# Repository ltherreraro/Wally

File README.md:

# Wally
## Recolector de basura espacios cerrados usando esp32 y RP2040
Es un dispositivo robótico con capacidad de navegación por  espacios abiertos y cerrados, reconocimiento y transmisión de imagen y video, con la finalidad de ver e identificar objetos del entorno y disponer de ellos (levantarlos, recogerlos y llevarlos a un sitio específico).  Inicialmente pensado para labores de aseo, puede ser fácilmente utilizado en otros entornos que por sus condiciones  representen un riesgo para la vida humana y animal (recintos con riesgos biológicos, edificios al borde del colapso, entre otros), que se puede validar a traves de una aplicacion
### ALCANCE
Durante la primera iteración, estamos trabajando para que Wally pueda recorrer un espacio cerrado relativamente pequeño (por ejemplo, un salón) evitando obstaculos y la identificación de objetos a través de la cámara de manera limitada.
### REQUERIMENTOS FUNCIONALES
Recepción y transmisión de imágenes, streaming video, detección de imágenes vía imagen y sensor ultrasonido, capacidad de navegación, recolección del objeto, conectividad inalámbrica (Wi-Fi, Bluetooth).
###REQUERIMENTOS NO FUNCIONALES
Estabilidad, fiabilidad, precisión el el reconocimiento y recolección de objeto, facilidad de uso.
### 
| Equipo | Corriente (in)| Voltaje (in)  |
| ------------- | ------------- |------------  |
| ESP32CAM | 500mA  |  3.3V -5V |
| NODEMCU  | 300mA  |  3,3V - 5V |
| SERVOR  | 400mA  |   5V |
| MOTOR  | 400mA  | 6V-9V |
| ULTRASONIO  | 15mA  |  5V  |
| L9110(PUENTE H)  | 0.5mA  | 2.5V-12V |
| MORSUN  | 800mA  |4.5v-36v  |

MORSUN: Salida 2000mA a 5V o 3,3V
### DIAGRAMA CAJA NEGRA
El módulo ESP32-CAM  sera el modulo principal tiene algunas características técnicas como son:

- Conectividad: WiFi 802.11b/g/n + Bluetooth 4.2 con BLE. Soporta carga de imagen por WiFi.
- Conexiones: UART, SPI, I2C, y PWM. Tiene 9 pines GPIO.
- Frecuencia de reloj: hasta 160Mhz.
- Potencia de cómputo del microcontrolador: hasta 600 DMIPS.
- Memoria: 520KB de SRAM +  4MB de PSRAM + SD slot para tarjetas
- Extras: tiene múltiples modos de reposo, firmware actualizable por OTA, y LED para uso de memoria flash built-in.
- Cámara: soporta cámaras OV2640 que pueden venir en el pack o comprarse independientemente. Este tipo de cámaras tienen:
- 2 MP en su sensor
- Tamaño de arreglo UXGA de 1622×1200 px
- Formato de salida YUV422, YUV420, RGB565, RGB555 y compresión de datos de 8-bit.
- Puede transferir imagen entre 15 y 60 FPS.

Adicionalmente se usara un modulo secundario ESP8266 para el control de los motores y **modulo ultrasonido**, el sistema en general tiene diferentes modulos como:
* Modulo de alimentacion: Consta de la bateria y el sistema de regulacion
* Modulo de movimiento: Inicialmente se plantea que se requiere un puente H de dos canales y dos motores.
* Modulo de movimiento detecion: Consta de un servomotor de 360 grados para rotar la camara 360
* Modulo de movimiento recolección: Inicialmente se plantea como dos servomotores
* Modulo de deteccion: Consta de una camara para reconocer basura y ultrasonido para detectar obstaculos tambien la cercania de los objetos
* Modulo de Indicadores y botones: Consta de leds para notificar al usuario conexion con el servidor, encendido, falla y botones de encendido tambien de reset.
 Modulo SD: Que se encargara de guardar las imagenes para ser enviadas en caso de perdida de conexion.

A continuacion se muestra un diagrama general

Finalmente los datasheet de los modulos a usar
- [ESP32](https://github.com/ltherreraro/Wally/blob/main/Datasheet/esp32-sl_specification.pdf)
- [ESP32CAM](https://github.com/ltherreraro/Wally/blob/main/Datasheet/ESP32-CAM%20Product%20Specification.pdf)
- [Nodemcu](https://www.make-it.ca/nodemcu-details-specifications/)
- [ESP8266](https://github.com/ltherreraro/Wally/blob/main/Datasheet/0a-esp8266ex_datasheet_en.pdf)
- [Servo MG90](https://github.com/ltherreraro/Wally/blob/main/Datasheet/MG90S_Tower-Pro%20(1).pdf)
- [Servo SG90](https://github.com/ltherreraro/Wally/blob/main/Datasheet/sg90_datasheet%20(1).pdf)
- [Motor](https://ferretronica.com/products/motorreductor-500-gr-cm-1000-rpm-6v?variant=12391693877341&currency=COP&utm_medium=product_sync&utm_source=google&utm_content=sag_organic&utm_campaign=sag_organic&utm_campaign=gs-2021-10-19&utm_source=google&utm_medium=smart_campaign&gclid=Cj0KCQjwjbyYBhCdARIsAArC6LKaKwvKPRHye8ZWSAgEkHbSm4rjs0Gm-KYxnCncWKSN3TIoLXUkZbEaAqU5EALw_wcB)
- [Ultrasonido](https://github.com/ltherreraro/Wally/blob/main/Datasheet/HCSR04%20(1).pdf)
- [Puente H](https://github.com/ltherreraro/Wally/blob/main/Datasheet/datasheet-l9110%20(1).pdf)
- [Regulador](https://github.com/ltherreraro/Wally/blob/main/Datasheet/2001081204_Shikues-AMS1117-1-2_C475600.pdf)
- [RP2040 pico](https://github.com/ltherreraro/Wally/blob/main/Datasheet/rp2040-datasheet.pdf)

#### Placa fabricada (Embebido)
Para este proyecto se diseño una placa con las condiciones necesarias para soportar el proyecto requerido, tanto en las corrientes que se aplican como en los circuitor integrados, dando como resultado, despues de impresión y ensamble, la siguiente placa: 

)
)
)

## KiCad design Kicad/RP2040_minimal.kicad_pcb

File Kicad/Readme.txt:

Vivan las drogas y el rock n roll!!

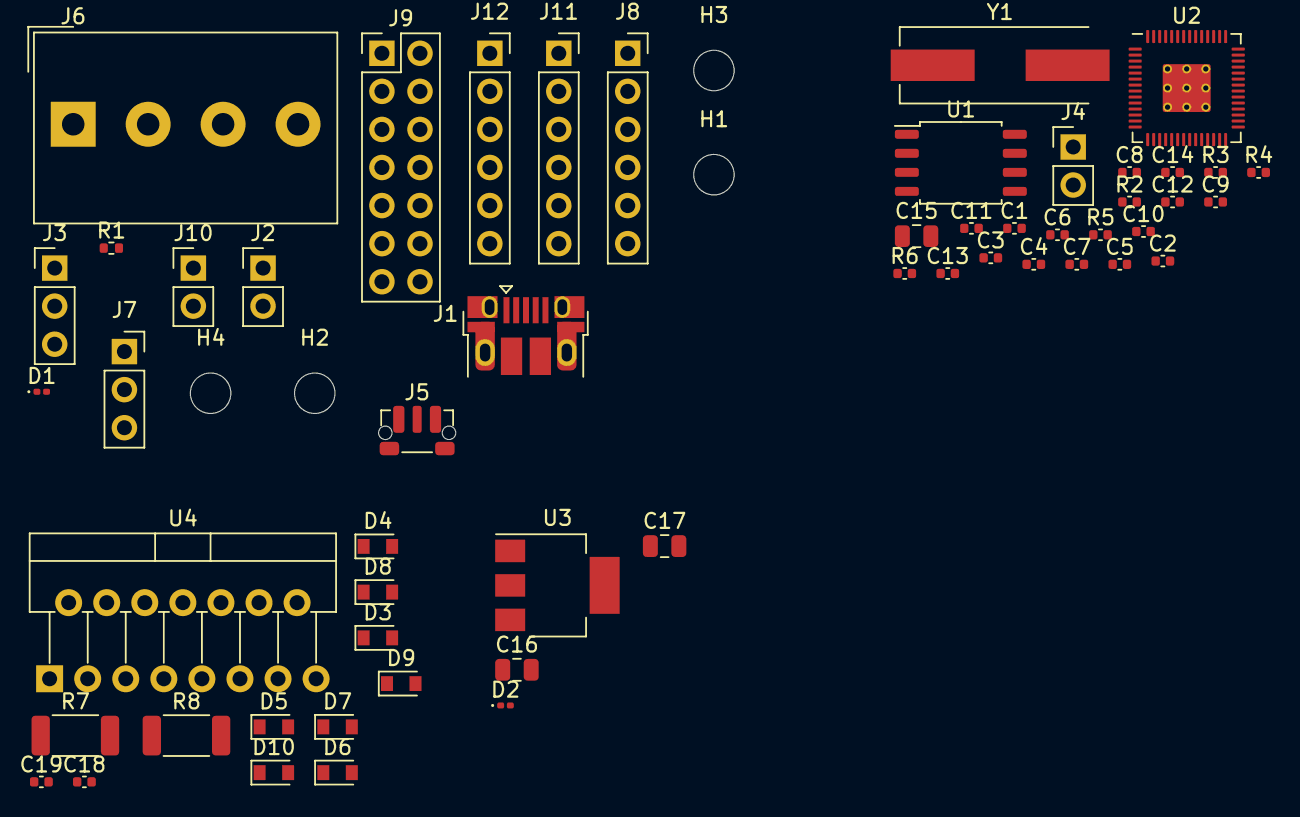
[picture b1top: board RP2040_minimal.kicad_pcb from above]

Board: 2 copper layers, 58 parts (0 on the bottom side), 43 nets, no tracks yet.

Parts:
C1, C2: 27p; C_0402_1005Metric
C3, C4, C5, C7, C9, C10, C11, C12, C13, C14, C18, C19: 100n; C_0402_1005Metric
C6, C8: 1u; C_0402_1005Metric
C15, C16, C17: 10u; C_0805_2012Metric
D1: LED; LED_0201_0603Metric
D2: D; D_0201_0603Metric
D3, D4, D5, D6, D7, D8, D9, D10: D_Schottky; D_SOD-110
H1, H2, H3, H4: MountingHole; MountingHole_2.7mm_M2.5
J1: USB_B_Micro; USB_Micro-B_Amphenol_10103594-0001LF_Horizontal_modified
J2, J4, J10: Conn_01x02; PinHeader_1x02_P2.54mm_Vertical
J3: Conn_01x03; PinHeader_1x03_P2.54mm_Vertical
J5: XLR3_Switched; SW_Push_1P1T-MP_NO_Horizontal_Alps_SKRTLAE010
J6: Screw_Terminal_01x04; Altech_AK300_1x04_P5.00mm_45-Degree
J7: Conn_01x03; PinSocket_1x03_P2.54mm_Vertical
J8, J11, J12: Conn_01x06; PinSocket_1x06_P2.54mm_Vertical
J9: Conn_02x07_Odd_Even; PinHeader_2x07_P2.54mm_Vertical
R1: R; R_0402_1005Metric
R2, R4: 1k; C_0402_1005Metric
R3: DNF; C_0402_1005Metric
R5, R6: 27; C_0402_1005Metric
R7, R8: 0.5; R_2010_5025Metric
U1: W25Q128JVS; SOIC-8_5.23x5.23mm_P1.27mm
U2: RP2040; RP2040-QFN-56
U3: NCP1117-3.3_SOT223; SOT-223-3_TabPin2
U4: L298N; TO-220-15_P2.54x2.54mm_StaggerOdd_Lead4.58mm_Vertical
Y1: ABLS-12.000MHZ-B4-T; Crystal_SMD_HC49-US

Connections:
+1V1: C4.1, C5.1, C6.1, U2.23 (DVDD), U2.45 (VREG_VOUT), U2.50 (DVDD)
+5V: C18.2, C19.1, D2.2 (A), D3.1 (K), D5.1 (K), D8.1 (K), D9.1 (K), J7.1, J8.1, J9.1, J9.3, J9.5, J9.7, J9.9, J9.11, J9.13, J11.1, J12.1, U4.4 (Vs), U4.9 (Vss)
/ECHO1: J8.3, U2.7 (GPIO5)
/ECHO2: J11.3, U2.9 (GPIO7)
/ECHO3: J12.3, U2.12 (GPIO9)
/FWD_A: U2.28 (GPIO17), U4.5 (IN1)
/FWD_B: U2.17 (GPIO14), U2.27 (GPIO16), U4.7 (IN2), U4.10 (IN3)
/OUT2_MOTORA: D5.2 (A), D6.1 (K), J6.3, U4.3 (OUT2)
/OUT2_MOTORB: D9.2 (A), D10.1 (K), J6.1, U4.14 (OUT4)
/OUT_MOTORB: D7.1 (K), D8.2 (A), J6.2, U4.13 (OUT3)
/PWM_SERVO1: J7.2, U2.2 (GPIO0)
/PWM_SERVO2: J7.3, U2.3 (GPIO1)
/PuenteH/OUT_MOTORA: D3.2 (A), D4.1 (K), U4.2 (OUT1)
/REV_B: U2.18 (GPIO15), U4.12 (IN4)
/RUN: J2.1, U2.26 (RUN)
/Rp2040/+3v3: C3.1, C7.1, C8.1, C9.1, C10.1, C11.1, C12.1, C13.1, C14.1, C15.1, R3.1, U1.8 (VCC), U2.1 (IOVDD), U2.10 (IOVDD), U2.22 (IOVDD), U2.33 (IOVDD), U2.42 (IOVDD), U2.43 (ADC_AVDD), U2.44 (VREG_IN), U2.48 (USB_VDD), U2.49 (IOVDD)
/Rp2040/GPIO25: R1.1, U2.37 (GPIO25)
/Rp2040/QSPI_SCLK: U1.6 (CLK), U2.52 (QSPI_SCLK)
/Rp2040/QSPI_SD0: U1.5 (DI(IO0)), U2.53 (QSPI_SD0)
/Rp2040/QSPI_SD1: U1.2 (DO(IO1)), U2.55 (QSPI_SD1)
/Rp2040/QSPI_SD2: U1.3 (IO2), U2.54 (QSPI_SD2)
/Rp2040/QSPI_SD3: U1.7 (IO3), U2.51 (QSPI_SD3)
/Rp2040/QSPI_SS: R2.1, R3.2, U1.1 (~CS), U2.56 (QSPI_SS)
/Rp2040/XIN: C1.1, U2.20 (XIN), Y1.1
/Rp2040/XOUT: R4.1, U2.21 (XOUT)
/Rp2040/~USB_BOOT: J4.1, R2.2
/SWCLK: J3.1, U2.24 (SWCLK)
/SWD: J3.3, U2.25 (SWD)
/TRIG1: J8.2, U2.8 (GPIO6)
/TRIG2: J11.2, U2.11 (GPIO8)
/TRIG3: J12.2, U2.13 (GPIO10)
/USB_D+: J1.3 (D+), R5.1
/USB_D-: J1.2 (D-), R6.1
/UartTX_Cam: J10.2, U2.15 (GPIO12)
GND: C1.2, C2.2, C3.2, C4.2, C5.2, C6.2, C7.2, C8.2, C9.2, C10.2, C11.2, C12.2, C13.2, C14.2, C15.2, C16.2, C17.2, C18.1, C19.2, D1.1 (K), D4.2 (A), D6.2 (A), D7.2 (A), D10.2 (A), J1.5 (GND), J1.6 (Shield), J2.2, J3.2, J4.2, J8.4, J9.2, J9.4, J9.6, J9.8, J9.10, J9.12, J9.14, J10.1, J11.4, J12.4, R7.2, R8.2, U1.4 (GND), U2.19 (TESTEN), U2.57 (GND), U3.1 (GND), U4.8 (GND)
unnamed: C2.1, R4.2, Y1.2
unnamed: C16.1, D2.1 (K), U3.3 (VI)
unnamed: C17.1, U3.2 (VO)
unnamed: D1.2 (A), R1.2
unnamed: R5.2, U2.47 (USB_DP)
unnamed: R6.2, U2.46 (USB_DM)
unnamed: R7.1, U4.1 (SENSE_A)
unnamed: R8.1, U4.15 (SENSE_B)

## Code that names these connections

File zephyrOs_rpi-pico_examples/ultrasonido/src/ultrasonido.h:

#ifndef USread
#define USread

/* The devicetree node identifier for the "led0" alias. */
#define ECHO_PIN5 DT_ALIAS(echo1)
#define TRIG_PIN6 DT_ALIAS(trig1)
#define ECHO_PIN7 DT_ALIAS(echo2)
#define TRIG_PIN8 DT_ALIAS(trig2)
#define ECHO_PIN9 DT_ALIAS(echo3)
#define TRIG_PIN10 DT_ALIAS(trig3)
#define ECHO_PIN18 DT_ALIAS(echo4)
#define TRIG_PIN26 DT_ALIAS(trig4)

void hola(void);
void getDistance(void);
void uscounter(uint8_t us);

#endif

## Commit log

2022-09-01 Datasheet
2022-09-01 Imagenes
2022-10-13 borrar key
2022-10-13 Esquematicos
2022-10-13 Readme kicad
2022-10-13 Datasheet RP2040
2022-10-13 README.md
2022-11-21 zephyrOs explamples rpi_pico
2022-11-21 delete
2022-11-21 examples-rpi_pico
2022-11-21 examples-rpi-pico
2022-11-21 documentacion-Example
2022-11-21 examples-raspberry-pico
2022-11-21 Readme_examples
2022-11-21 Update README.md
    Arreglo
2022-11-21 Readme
2022-12-05 modelo 3d
2022-12-06 Control
2022-12-06 data
2022-12-07 ultasonido
2022-12-07 documentacion
2022-12-07 Create CNAME
2022-12-07 documenta
2022-12-07 HTML
2022-12-07 docs
2022-12-07 motores
2022-12-07 servo
2022-12-07 entorno de simulacion
